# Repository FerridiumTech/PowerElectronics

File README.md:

# PowerElectronics
Circuit simulations &amp; PCB designs

This repo contains the circuits simulations and PCB designs I have done while learning general electronics and power electronics.

## PCBs
These have been designed using KiCAD 9 and KiCAD 10.
Just open the project files in KiCAD to view the schematics and pcb layout. You can use the HQ DFM software (Windows only) or its plugin in KiCAD if interested in Design for Manufucturing.

## Electronics Circuits Simulations
Being a heavy user of GNU/Linux, opensource and free software I have used QUCS-S [https://github.com/ra3xdh/qucs_s] with Ngspice [https://ngspice.sourceforge.io/] as the simulation kernel. Qucs with SPICE offers a nice GUI for instruments of  schematic capture, visualization and provides different passive and active components including a very rich device library that is updated regularly.

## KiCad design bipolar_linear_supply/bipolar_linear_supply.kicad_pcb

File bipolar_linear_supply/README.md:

## Bipolar Linear Power Supply
This dual-polarity linear power supply, from ***Practical Electronics for Inventors - Paul Scherz***  will provide any positive or negative voltage between 1.2 and
35 V. The complementary regulators—LM317 (+) and LM337 (-)—can deliver up to 1.5 A (output voltage dependent) if
provided adequate heat sinking. 

This is sufficient for testing or powering a wide variety of everyday circuits. The key is
the center-tap transformer with secondary tapped to ground that supplies both positive and negative voltages relative to
ground. It converts the line voltage from 120 VAC to 48 VAC at the secondary, which is center-tapped and divided into
24-VAC portions. By using the center tap as a ground or common connection, it is possible to get both positive and nega-
tive outputs relative to ground. 

The diodes rectify the ac from the transformer output into a pulsing dc waveform. C1 and
C2 electrolytic capacitors perform bulk filtering of the pulsing dc waveform, resulting in a raw dc voltage. C3 and C4 are
small film capacitors bypassing the electrolytic capacitors to improve transient response and filter high-frequency line
noise. The LM317 (+) and LM337 (-) are complementary adjustable voltage regulators, whose output can be programmed
with two external resistors. C5 and C6 improve the regulators’ ripple rejection from 65 dB to 80 dB by preventing ripple voltage from being amplified
at the output of the regulator. C7 and C8 electrolytic capacitors stiffen the output voltage and reduce output impedance. C9
and C10 are small bypass capacitors to filter any high-frequency noise present at the output. All bypass capacitors should
have low impedance (e.g., polyester, polypropylene, polystyrene, or Mylar film capacitors are okay). A 48-VAC CT (24-0-24)
transformer is about the practical upper limit of commonly available models. This limit is set by the maximum input
voltage of the regulators, and also by the bulk filter capacitors that are rated at 35 VDC.

### NB
MAKE SURE TO HEATSINK BOTH VOLTAGE REGULATORS

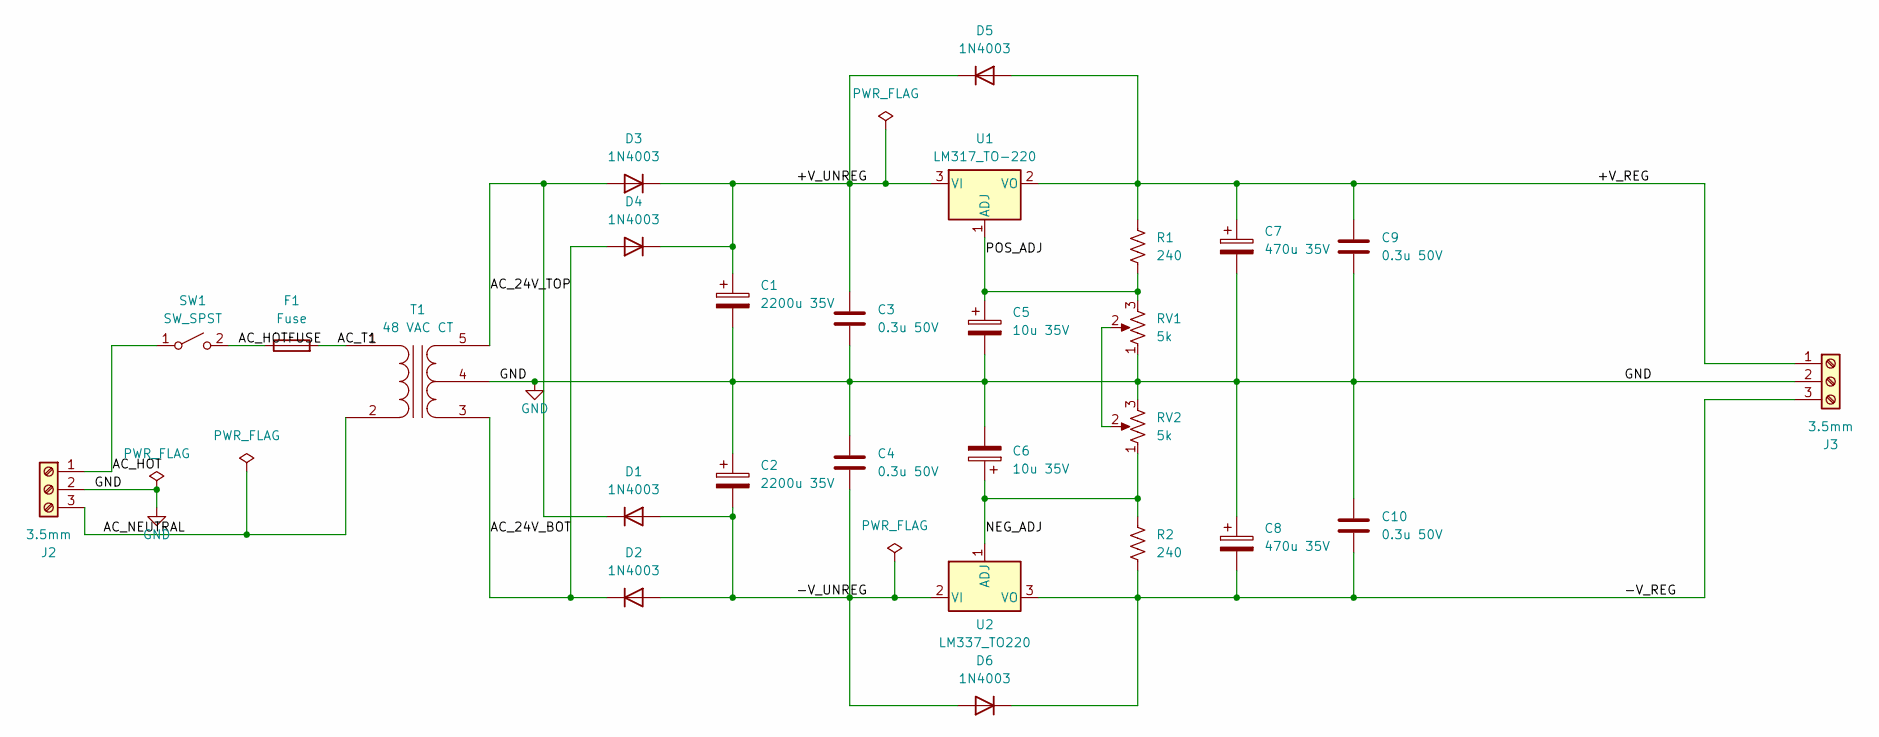
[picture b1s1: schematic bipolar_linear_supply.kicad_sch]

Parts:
C1, C2: 2200u 35V; CP_Radial_D10.0mm_P3.80mm
C3, C4: 0.3u 50V; C_Disc_D5.0mm_W2.5mm_P2.50mm
C5, C6: 10u 35V; CP_Radial_D10.0mm_P3.80mm
C7, C8: 470u 35V; CP_Radial_D8.0mm_P3.50mm
C9, C10: 0.3u 50V; CP_Radial_Tantal_D5.0mm_P5.00mm
D1, D2, D3, D4, D5, D6: 1N4003; D_DO-41_SOD81_P10.16mm_Horizontal
F1: Fuse; Fuse_1210_3225Metric_Pad1.42x2.65mm_HandSolder
J2, J3: 3.5mm; ScrewTerminal_1x03_P3.5mm_Horizontal_Black
R1, R2: 240; R_Axial_DIN0204_L3.6mm_D1.6mm_P7.62mm_Horizontal
RV1, RV2: 5k; Potentiometer_Bourns_3266W_Vertical
SW1: SW_SPST; SW_SPST_REED_CT05-XXXX-G1
T1: 48 VAC CT; Transformer_MACOM_SM-22
U1: LM317_TO-220; TO-220-3_Vertical
U2: LM337_TO220; TO-220-3_Vertical

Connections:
/+V_REG: C7.1, C9.1, D5.2 (A), J3.1, R1.1, U1.2 (VO)
/+V_UNREG: C1.1, C3.1, D3.1 (K), D4.1 (K), D5.1 (K), U1.3 (VI)
/-V_UNREG: C2.2, C4.2, D1.2 (A), D2.2 (A), D6.2 (A), U2.2 (VI)
/<NO NET>: C8.2, C10.2, D6.1 (K), J3.3, R2.2, U2.3 (VO)
/AC_24V_BOT: D2.1 (K), D4.2 (A), T1.3 (SA)
/AC_24V_TOP: D1.1 (K), D3.2 (A), T1.5 (SB)
/AC_HOT: J2.1, SW1.1 (A)
/AC_HOTFUSE: F1.1, SW1.2 (B)
/AC_NEUTRAL: J2.3, T1.2 (AB)
/AC_T1: F1.2, T1.1 (AA)
/NEG_ADJ: C6.1, R2.1, RV2.1, U2.1 (ADJ)
/POS_ADJ: C5.1, R1.2, RV1.3, U1.1 (ADJ)
GND: C1.2, C2.1, C3.2, C4.1, C5.2, C6.2, C7.2, C8.1, C9.2, C10.1, J2.2, J3.2, RV1.1, RV2.3, T1.4 (SC)
unnamed: RV1.2, RV2.2

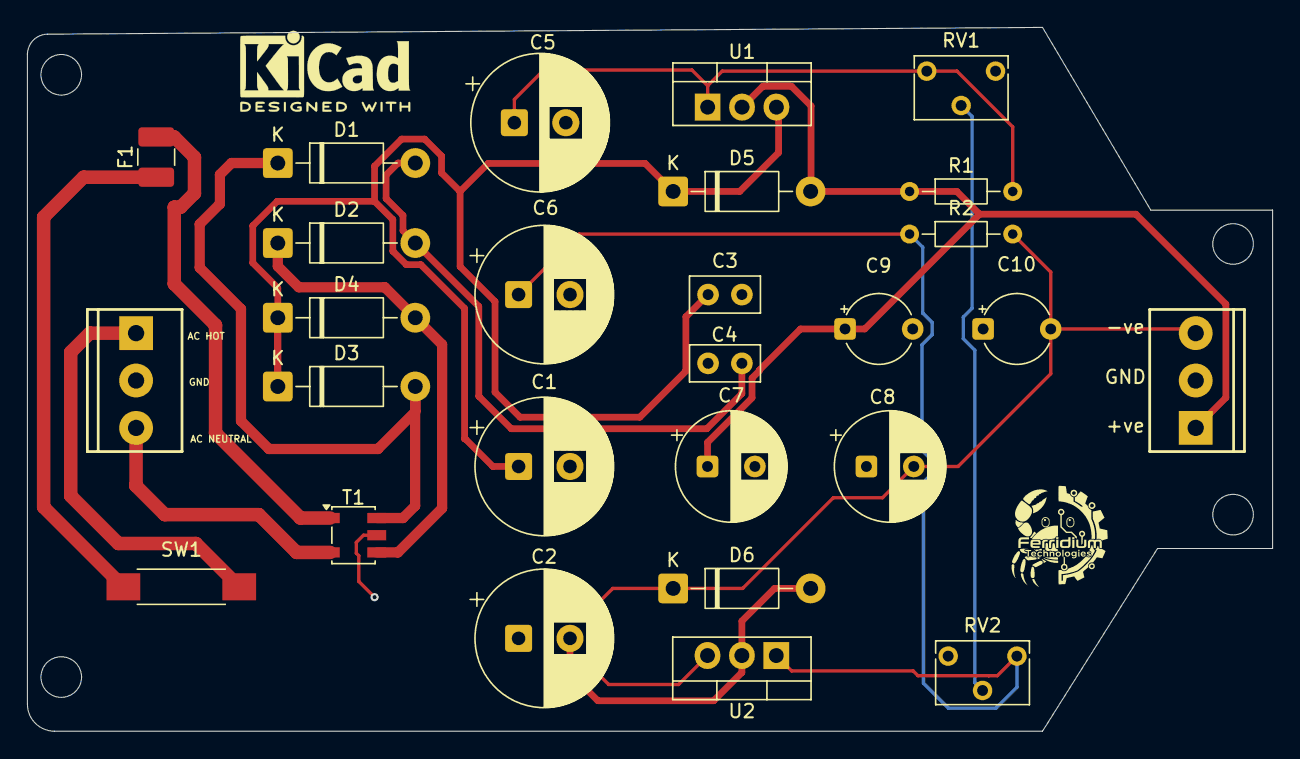
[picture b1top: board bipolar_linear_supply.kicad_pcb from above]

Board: 2 copper layers, 92.0 x 52.0 mm, 27 parts (0 on the bottom side), 14 nets.

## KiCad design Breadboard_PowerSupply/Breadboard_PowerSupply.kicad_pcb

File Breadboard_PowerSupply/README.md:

# BreadBoard Power Supply
When building circuits on the breadboard and you need more power than your MCU can provide, you need something better than your bench power supply which is noisy (large cooling fan) and needs some setup to tune voltage and current.

So we need something that:
- Plugs directly on the breadboard; therefore, no wires exist.
- Have an on/off switch.
- Can provide 5V and 3.3V power.
- Power can be drawn from various wall power supplies, from 6V to 12V.

The design considered the constraints of common breadboard and I came up with this:

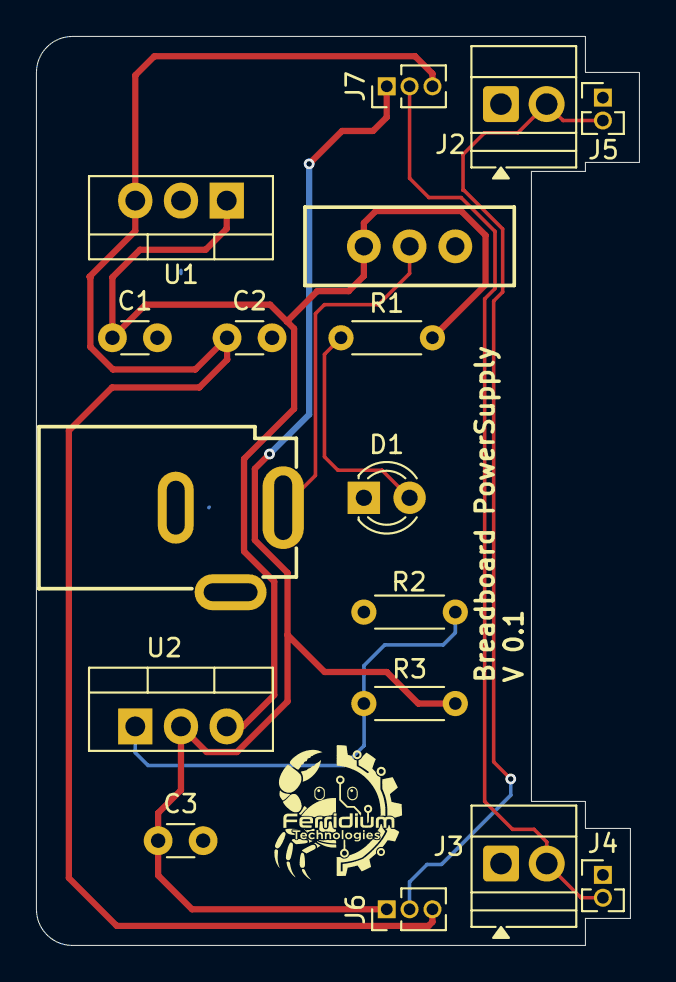
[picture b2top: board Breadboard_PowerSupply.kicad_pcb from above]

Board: 2 copper layers, 33.5 x 50.5 mm, 17 parts (0 on the bottom side), 9 nets.

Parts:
C1: 10u; C_Disc_D3.0mm_W1.6mm_P2.50mm
C2: 0.1u; C_Disc_D3.0mm_W1.6mm_P2.50mm
C3: 1u; C_Disc_D3.0mm_W1.6mm_P2.50mm
D1: LED; LED_D3.0mm
J1: Barrel_Jack_PTH_Slot
J2, J3: Screw_Terminal_01x02; TerminalBlock_Xinya_XY308-2.54-2P_1x02_P2.54mm_Horizontal
J4, J5: Conn_01x02_Pin; PinHeader_1x02_P1.27mm_Vertical
J6, J7: Conn_01x03_Pin; PinHeader_1x03_P1.27mm_Vertical
R1, R2: 330; R_Axial_DIN0204_L3.6mm_D1.6mm_P5.08mm_Horizontal
R3: 560; R_Axial_DIN0204_L3.6mm_D1.6mm_P5.08mm_Horizontal
SW1: SPDT_Slide_PTH_11.6x4.0mm-ShortPin; Slide_SPDT_PTH_11.6x4.0mm
U1: LM7805_TO220; TO-220-3_Vertical
U2: LM317_TO-220; TO-220-3_Vertical

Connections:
/3.3V: C3.1, J6.1, J7.1, R3.2, U2.2 (VO)
/5V: C2.1, J6.3, J7.3, U1.3 (VO)
/12V: C1.1, R1.2, SW1.1 (A), U1.1 (VI), U2.3 (VI)
/POWER_OUT_BOT: J3.2, J4.2, J7.2
/POWER_OUT_TOP: J2.2, J5.2, J6.2
/Power_input: J1.PWR, SW1.2 (B)
GND: C1.2, C2.2, C3.2, D1.1 (K), J1.GND, J1.GNDBREAK, J2.1, J3.1, J4.1, J5.1, R2.1, U1.2 (GND)
unnamed: D1.2 (A), R1.1
unnamed: R2.2, R3.1, U2.1 (ADJ)
